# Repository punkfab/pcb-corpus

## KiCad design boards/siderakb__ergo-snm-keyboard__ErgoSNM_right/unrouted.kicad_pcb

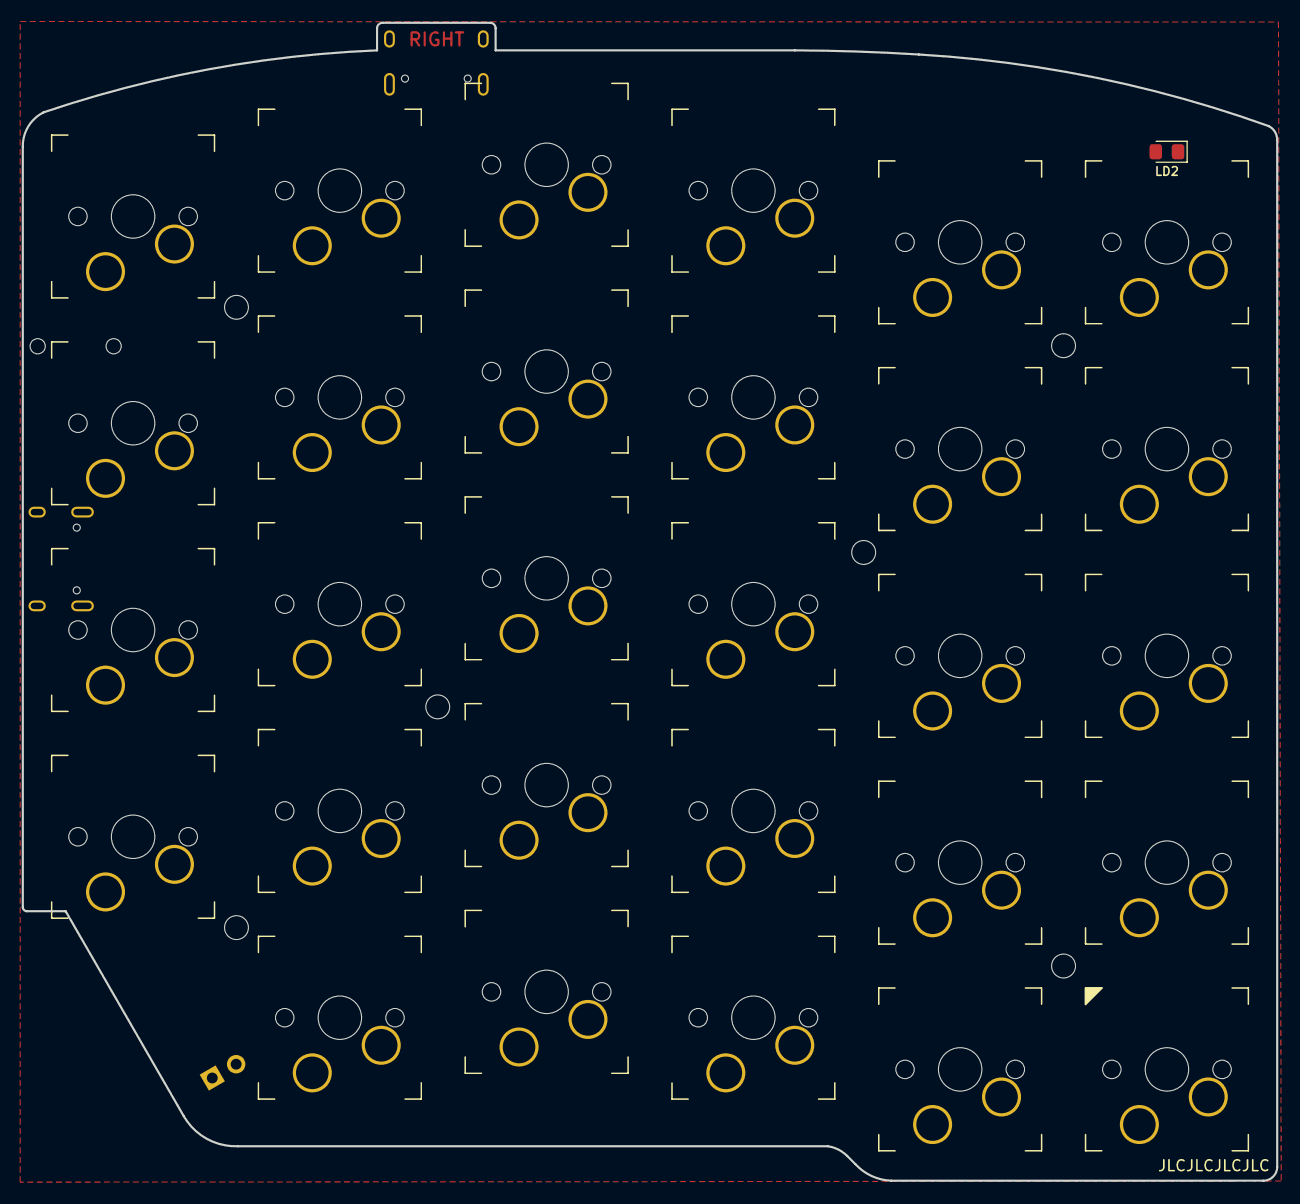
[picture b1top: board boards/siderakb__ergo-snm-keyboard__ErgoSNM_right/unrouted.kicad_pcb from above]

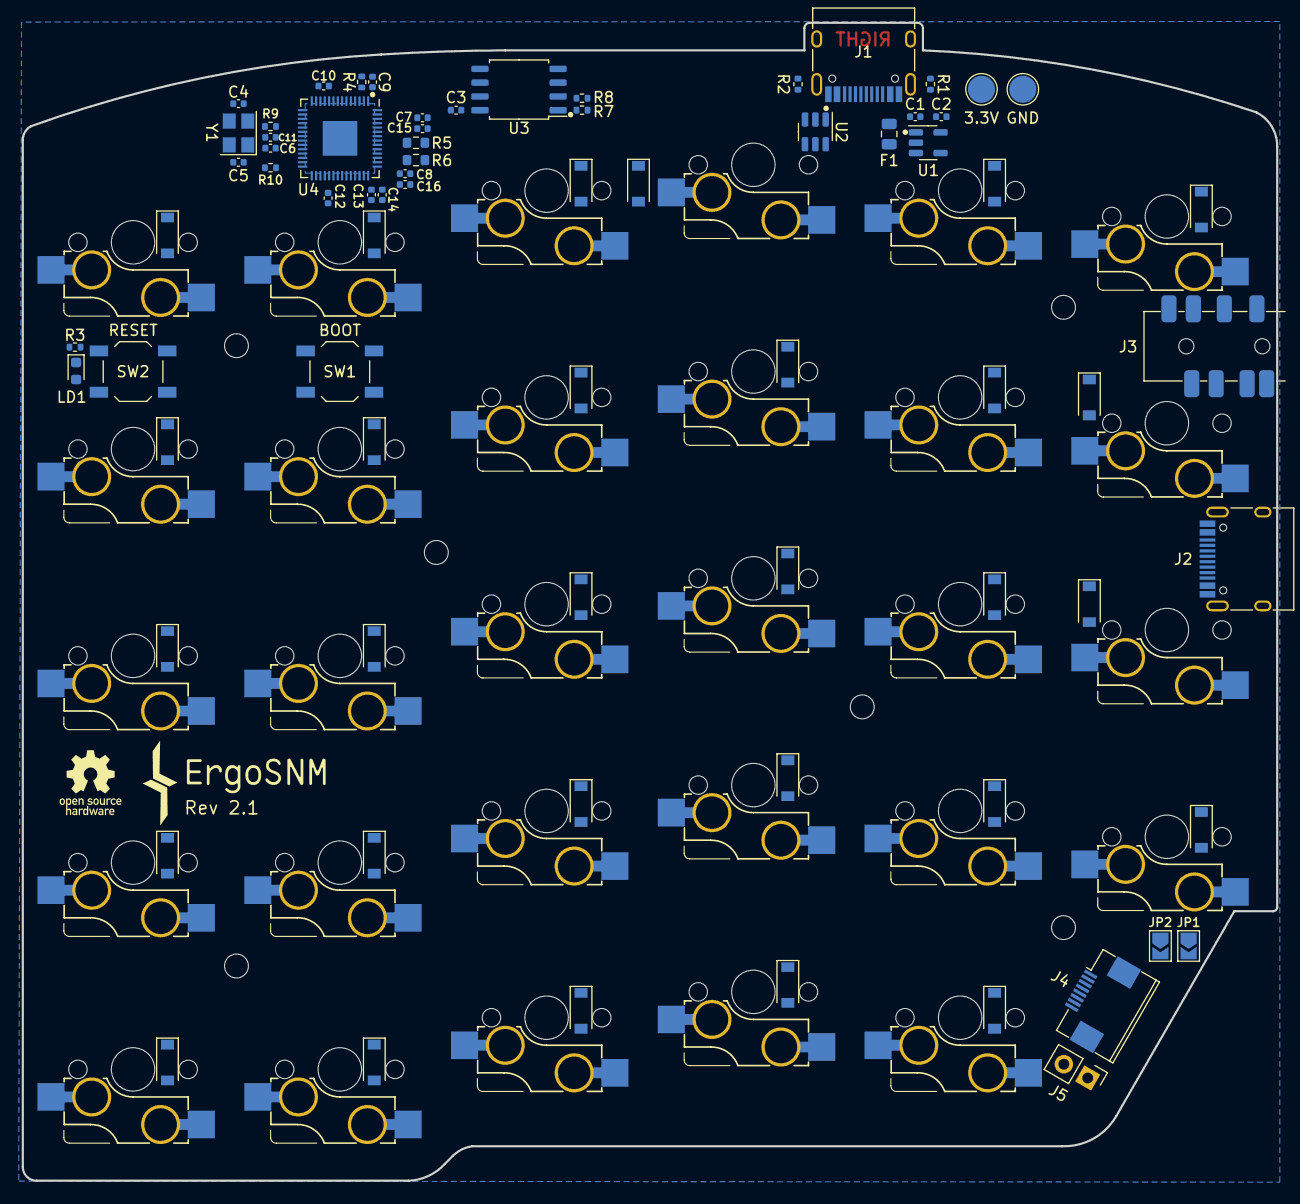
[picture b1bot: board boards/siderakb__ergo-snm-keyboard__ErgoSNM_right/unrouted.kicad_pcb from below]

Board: 2 copper layers, 115.6 x 106.7 mm, 109 parts (73 on the bottom side), 71 nets, no tracks yet.

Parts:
C1, C2, C8, C16: 1uF; C_0402_1005Metric
C3, C6, C7, C9, C10, C11, C12, C13, C14, C15: 100nF; C_0402_1005Metric
C4, C5: 20pF; C_0402_1005Metric
D1, D2, D3, D4, D5, D6, D7, D8, D9, D10, D11, D12, D13, D14, D15, D16, D17, D18, D19, D20, D21, D22, D23, D24, D25, D26, D27, D28, D29: 1N4148; D_SOD-123
F1: 500mA, 6V; Fuse_0805_2012Metric
H1, H2, H3, H4, H5, H6: MountingHole; MountingHole_2.2mm_M2
J1, J2: USB_C_Receptacle_USB2.0; USB_C_Receptacle_HRO_TYPE-C-31-M-12
J3: PJ-393_TRRS_8P; PJ-393 8P TRRS
J4: Conn_01x08; FPC_8P_0.5mm_AFC01-S08FCA-00
J5: Conn_01x02; PinHeader_1x02_P2.54mm_Vertical
JP1, JP2: SolderJumper_2_Open; SolderJumper-2_P1.3mm_Open_TrianglePad1.0x1.5mm
KEY1, KEY2, KEY3, KEY4, KEY5, KEY6, KEY7, KEY8, KEY9, KEY10, KEY11, KEY12, KEY13, KEY14, KEY15, KEY16, KEY17, KEY18, KEY19, KEY20, KEY21, KEY22, KEY23, KEY24, KEY25, KEY26, KEY27, KEY28, KEY29: SW_Push_45deg; MX_switch_PTH_hotswap_A
LD1: Red; LED_0603_1608Metric
LD2: LED; LED_0805_2012Metric_Pad1.15x1.40mm_HandSolder
R1, R2, R4: 5.1k; R_0402_1005Metric
R3, R7, R9: 1k; R_0402_1005Metric
R5, R6: 27; R_0603_1608Metric
R8, R10: 10k; R_0402_1005Metric
SW1: BOOT; SW_SPST_TL3342
SW2: RESET; SW_SPST_TL3342
TP1, TP4: TestPoint; TestPoint_Pad_D2.5mm
U1: RT9013-33GB; SOT-23-5
U2: SRV05-4; SOT-23-6
U3: W25Q128JVS; SOIC-8_5.23x5.23mm_P1.27mm
U4: RP2040; QFN-56-1EP_7x7mm_P0.4mm_EP3.2x3.2mm
Y1: 12MHz; Crystal_SMD_3225-4Pin_3.2x2.5mm

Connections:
+1V1: C6.1, C7.1, C8.1, U4.23 (DVDD), U4.45 (VREG_VOUT), U4.50 (DVDD)
+3V3: C2.1, C3.1, C9.1, C10.1, C11.1, C12.1, C13.1, C14.1, C15.1, C16.1, J2.A4 (VBUS), J2.A9 (VBUS), J2.B4 (VBUS), J2.B9 (VBUS), J3.S, J4.7, R4.2, R8.1, R10.1, TP1.1, U1.5 (VOUT), U3.8 (VCC), U4.1 (IOVDD), U4.10 (IOVDD), U4.22 (IOVDD), U4.33 (IOVDD), U4.42 (IOVDD), U4.43 (ADC_AVDD), U4.44 (VREG_IN), U4.48 (USB_VDD), U4.49 (IOVDD)
+5V: C1.1, F1.2, U1.1 (VIN), U1.3 (EN), U2.5 (VP)
/RP2040/BOOT: R7.1, SW1.2
/RP2040/QSPI_D0: U3.5 (DI(IO0)), U4.53 (QSPI_SD0)
/RP2040/QSPI_D1: U3.2 (DO(IO1)), U4.55 (QSPI_SD1)
/RP2040/QSPI_D2: U3.3 (IO2), U4.54 (QSPI_SD2)
/RP2040/QSPI_D3: U3.7 (IO3), U4.51 (QSPI_SD3)
/RP2040/QSPI_SCLK: U3.6 (CLK), U4.52 (QSPI_SCLK)
/RP2040/QSPI_SS: R7.2, R8.2, U3.1 (~CS), U4.56 (QSPI_SS)
/RP2040/~RESET: R10.2, SW2.2, U4.26 (RUN)
/USB_D+: J1.A6 (D+), J1.B6 (D+), R5.1, U2.3 (IO2)
/USB_D-: J1.A7 (D-), J1.B7 (D-), R6.1, U2.4 (IO3)
COL_0: KEY1.1, KEY7.1, KEY13.1, KEY19.1, KEY25.1, U4.15 (GPIO12)
COL_1: KEY2.1, KEY8.1, KEY14.1, KEY20.1, KEY26.1, U4.29 (GPIO18)
COL_2: KEY3.1, KEY9.1, KEY15.1, KEY21.1, KEY27.1, U4.14 (GPIO11)
COL_3: KEY4.1, KEY10.1, KEY16.1, KEY22.1, KEY28.1, U4.30 (GPIO19)
COL_4: KEY5.1, KEY11.1, KEY17.1, KEY23.1, KEY29.1, U4.37 (GPIO25)
COL_5: J5.1, JP2.1 (A), KEY6.1, KEY12.1, KEY18.1, KEY24.1, U4.39 (GPIO27_ADC1)
GND: C1.2, C2.2, C3.2, C4.1, C5.1, C6.2, C7.2, C8.2, C9.2, C10.2, C11.2, C12.2, C13.2, C14.2, C15.2, C16.2, J1.A1 (GND), J1.A12 (GND), J1.B1 (GND), J1.B12 (GND), J1.S1 (SHIELD), J2.A1 (GND), J2.A12 (GND), J2.B1 (GND), J2.B12 (GND), J2.S1 (SHIELD), J3.T, J4.8, R1.2, R2.2, R3.2, SW1.1, SW2.1, TP4.1, U1.2 (GND), U2.2 (VN), U3.4 (GND), U4.18 (GPIO15), U4.19 (TESTEN), U4.57 (GND), Y1.2, Y1.4
MISO: J4.5, U4.31 (GPIO20)
MOSI: J4.4, U4.35 (GPIO23)
unnamed: C4.2, U4.20 (XIN), Y1.3
unnamed: C5.2, R9.1, Y1.1
unnamed: D1.2 (A), KEY1.2
unnamed: D2.2 (A), KEY2.2
unnamed: D3.2 (A), KEY3.2
unnamed: D4.2 (A), KEY4.2
unnamed: D5.2 (A), KEY5.2
unnamed: D6.2 (A), KEY6.2
unnamed: D7.2 (A), KEY7.2
unnamed: D8.2 (A), KEY8.2
unnamed: D9.2 (A), KEY9.2
unnamed: D10.2 (A), KEY10.2
unnamed: D11.2 (A), KEY11.2
unnamed: D12.2 (A), KEY12.2
unnamed: D13.2 (A), KEY13.2
unnamed: D14.2 (A), KEY14.2
unnamed: D15.2 (A), KEY15.2
unnamed: D16.2 (A), KEY16.2
unnamed: D17.2 (A), KEY17.2
unnamed: D18.2 (A), KEY18.2
unnamed: D19.2 (A), KEY19.2
unnamed: D20.2 (A), KEY20.2
unnamed: D21.2 (A), KEY21.2
unnamed: D22.2 (A), KEY22.2
unnamed: D23.2 (A), KEY23.2
unnamed: D24.2 (A), KEY24.2
unnamed: D25.2 (A), KEY25.2
unnamed: D26.2 (A), KEY26.2
unnamed: D27.2 (A), KEY27.2
unnamed: D28.2 (A), KEY28.2
unnamed: D29.2 (A), KEY29.2
unnamed: J1.A5 (CC1), R1.1
unnamed: J1.B5 (CC2), R2.1
unnamed: J4.1, JP2.2 (B)
unnamed: J4.2, JP1.2 (B)
unnamed: LD1.1 (K), LD2.1 (K), R3.1
unnamed: R5.2, U4.47 (USB_DP)
unnamed: R6.2, U4.46 (USB_DM)
unnamed: R9.2, U4.21 (XOUT)
ROW_0: D1.1 (K), D2.1 (K), D3.1 (K), D4.1 (K), D5.1 (K), D6.1 (K), U4.41 (GPIO29_ADC3)
ROW_1: D7.1 (K), D8.1 (K), D9.1 (K), D10.1 (K), D11.1 (K), D12.1 (K), U4.12 (GPIO9)
ROW_2: D13.1 (K), D14.1 (K), D15.1 (K), D16.1 (K), D17.1 (K), D18.1 (K), U4.8 (GPIO6)
ROW_3: D19.1 (K), D20.1 (K), D21.1 (K), D22.1 (K), D23.1 (K), D24.1 (K), U4.6 (GPIO4)
ROW_4: D25.1 (K), D26.1 (K), D27.1 (K), D28.1 (K), D29.1 (K), J5.2, JP1.1 (A), U4.4 (GPIO2)
SCLK: J4.3, U4.34 (GPIO22)
SERIAL: J2.A6 (D+), J2.B6 (D+), J3.R1, R4.1, U4.2 (GPIO0)
STATE_LED: LD1.2 (A), LD2.2 (A), U4.28 (GPIO17)
VBUS: F1.1, J1.A4 (VBUS), J1.A9 (VBUS), J1.B4 (VBUS), J1.B9 (VBUS)
~CS: J4.6, U4.32 (GPIO21)

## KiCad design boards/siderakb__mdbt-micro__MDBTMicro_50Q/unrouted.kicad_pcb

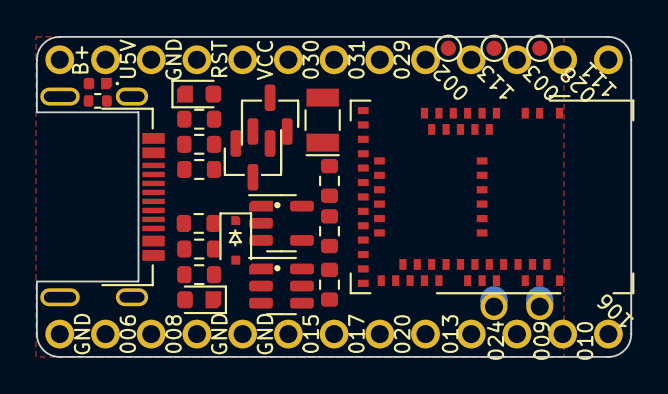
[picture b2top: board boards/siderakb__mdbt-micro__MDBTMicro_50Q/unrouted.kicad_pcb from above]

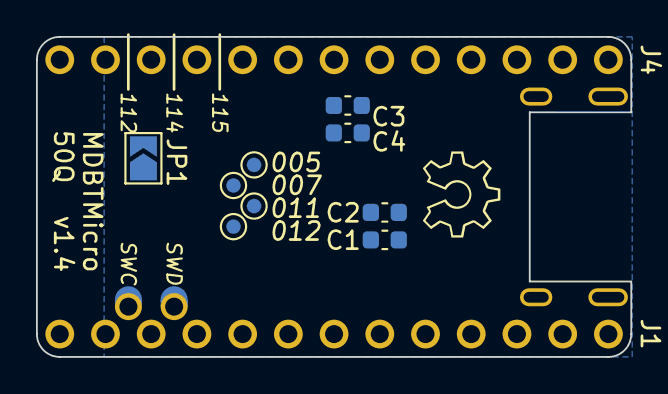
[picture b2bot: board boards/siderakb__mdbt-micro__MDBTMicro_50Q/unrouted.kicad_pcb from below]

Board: 2 copper layers, 33.0 x 17.8 mm, 36 parts (11 on the bottom side), 49 nets, no tracks yet.

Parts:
C1, C2: 1uF; C_0603_1608Metric
C3, C4: 12pF; C_0603_1608Metric
D1: 1N5819; D_SOD-323F
J1, J4: Conn_01x13; PinHeader_1x13_P2.54mm_Vertical
J2: USB_C_Receptacle_USB2.0; USB Type-C Mid-Mount Receptacle 16P
J3: Conn_01x02; PinHeader_1x02_P2.54mm_Vertical
JP1: SolderJumper_2_Open; SolderJumper-2_P1.3mm_Open_TrianglePad1.0x1.5mm
LD1: Red; LED_0603_1608Metric
LD2: Blue; LED_0603_1608Metric
LD3: Green; LED_0402_1005Metric
Q1, Q2: AO3407; SOT-23
R1: 100k; R_0603_1608Metric
R2, R4: 1k; R_0603_1608Metric
R3: Rprog; R_0603_1608Metric
R5: 1k; R_0402_1005Metric
R6: 820k; R_0603_1608Metric
R7, R8: 2M; R_0603_1608Metric
R9, R10: 5.1k; R_0603_1608Metric
TP1, TP2, TP3, TP4, TP5, TP6, TP7: TestPoint; TestPoint_Pad_D1.0mm
U1: XC6220B331MR-G; SOT-23-5
U2: MDBT50Q-x1MV2; Raytac_MDBT50Q
U3: TP4057; SOT-23-6
X1: 32.768kHz; Crystal_SMD_MicroCrystal_CC7V-T1A-2Pin_3.2x1.5mm

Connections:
/P0.02: J4.9, U2.11 (P0.02/AIN0)
/P0.03: J4.11, U2.9 (P0.03/AIN1)
/P0.05: TP4.1, U2.21 (P0.05/AIN3)
/P0.06: J1.2, U2.22 (P0.06)
/P0.07: TP5.1, U2.23 (TRACECLK/P0.07)
/P0.08: J1.3, U2.24 (P0.08)
/P0.09: J1.11, U2.52 (P0.09/NFC1)
/P0.10: J1.12, U2.54 (P0.10/NFC2)
/P0.11: TP6.1, U2.27 (TRACEDATA2/P0.11)
/P0.12: TP7.1, U2.29 (TRACEDATA1/P0.12)
/P0.13: J1.9, U2.37 (P0.13)
/P0.15: J1.6, U2.39 (P0.15)
/P0.17: J1.7, U2.41 (P0.17)
/P0.20: J1.8, U2.44 (P0.20)
/P0.24: J1.10, U2.48 (P0.24)
/P0.28: J4.12, U2.13 (P0.28/AIN4)
/P0.29: J4.8, U2.10 (P0.29/AIN5)
/P0.30: J4.6, U2.14 (P0.30/AIN6)
/P0.31: J4.7, U2.12 (P0.31/AIN7)
/P1.04: JP1.1 (A), U2.56 (P1.04)
/P1.06: J1.13, U2.57 (P1.06)
/P1.11: J4.13, JP1.2 (B), U2.4 (P1.11)
/P1.12: TP1.1, U2.5 (P1.12)
/P1.13: J4.10, U2.6 (P1.13)
/P1.14: TP2.1, U2.7 (P1.14)
/P1.15: TP3.1, U2.8 (P1.15)
BATTERY_PIN: R6.1, R7.2, U2.20 (P0.04/AIN2)
EXT_VCC: J4.5, Q2.3 (D)
GND: C1.2, C2.2, C3.1, C4.1, J1.1, J1.4, J1.5, J2.A1 (GND), J2.A12 (GND), J2.B1 (GND), J2.B12 (GND), J2.S1 (SHIELD), J4.3, R1.2, R3.1, R4.1, R5.1, R7.1, R8.2, R9.2, R10.2, U1.2 (VSS), U2.1 (GND), U2.2 (GND), U2.15 (GND), U2.33 (GND), U2.55 (GND), U3.2 (GND)
LED_PIN: LD2.2 (A), U2.3 (P1.10)
unnamed: C1.1, D1.1 (K), Q1.2 (S), U1.1 (VIN), U1.3 (CE)
unnamed: C3.2, U2.17 (XL1/P0.00), X1.2
unnamed: C4.2, U2.18 (XL2/P0.01), X1.1
unnamed: J2.A5 (CC1), R9.1
unnamed: J2.B5 (CC2), R10.1
unnamed: LD1.1 (K), U3.1 (CHRG)
unnamed: LD1.2 (A), R2.1
unnamed: LD2.1 (K), R4.2
unnamed: LD3.1 (K), R5.2
unnamed: R3.2, U3.6 (PROG)
POWER_PIN: Q2.1 (G), R8.1, U2.26 (TRACEDATA3/P1.09)
RESET: J4.4, U2.40 (~RESET/P0.18)
SWCLK: J3.2, U2.53 (SWDCLK)
SWDIO: J3.1, U2.51 (SWDIO)
USB_D+: J2.A6 (D+), J2.B6 (D+), U2.35 (D+)
USB_D-: J2.A7 (D-), J2.B7 (D-), U2.34 (D-)
VBAT: J4.1, Q1.3 (D), R6.2, U3.3 (BAT)
VBUS: D1.2 (A), J2.A4 (VBUS), J2.A9 (VBUS), J2.B4 (VBUS), J2.B9 (VBUS), J4.2, LD3.2 (A), Q1.1 (G), R1.1, R2.2, U2.32 (VBUS), U3.4 (VCC)
nRF_VDD: C2.1, Q2.2 (S), U1.5 (VOUT), U2.28 (VDD), U2.30 (VDDH)

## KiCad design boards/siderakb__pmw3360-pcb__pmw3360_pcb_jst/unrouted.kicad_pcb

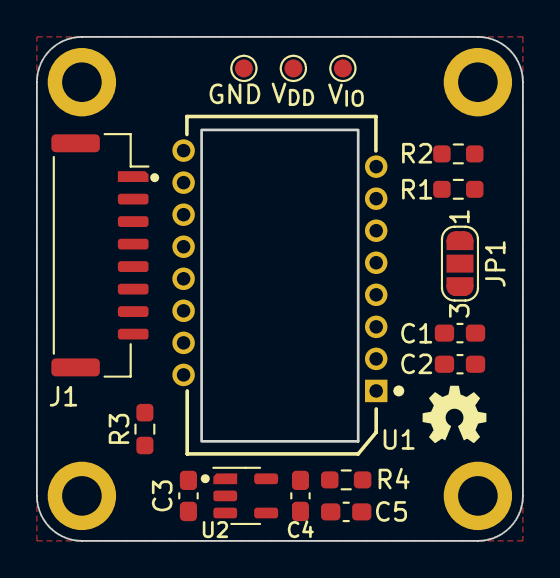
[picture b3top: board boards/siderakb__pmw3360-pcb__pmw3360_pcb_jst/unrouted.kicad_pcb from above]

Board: 2 copper layers, 27.0 x 28.0 mm, 20 parts (0 on the bottom side), 13 nets, no tracks yet.

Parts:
C1: 4.7uF/10V; C_0603_1608Metric_Pad1.08x0.95mm_HandSolder
C2: 100nF; C_0603_1608Metric_Pad1.08x0.95mm_HandSolder
C3: 1uF; C_0603_1608Metric_Pad1.08x0.95mm_HandSolder
C4: 4.7uF; C_0603_1608Metric_Pad1.08x0.95mm_HandSolder
C5: 22nF; C_0603_1608Metric_Pad1.08x0.95mm_HandSolder
H1, H2, H3, H4: MountingHole_Pad; MountingHole_2.2mm_M2_ISO14580_Pad
J1: Conn_01x08; JST_GH_SM08B-GHS-TB_1x08-1MP_P1.25mm_Horizontal
JP1: SolderJumper_3_Open; SolderJumper-3_P1.3mm_Open_RoundedPad1.0x1.5mm_NumberLabels
R1, R2: 10k; R_0603_1608Metric_Pad0.98x0.95mm_HandSolder
R3: 39R; R_0603_1608Metric_Pad0.98x0.95mm_HandSolder
R4: 28k; R_0603_1608Metric_Pad0.98x0.95mm_HandSolder
TP1: V_{IO}; TestPoint_Pad_D1.0mm
TP2: V_{DD}; TestPoint_Pad_D1.0mm
TP3: GND; TestPoint_Pad_D1.0mm
U1: PMW3360DM-T2QU; PMW3360DM-T2QU 16Pin
U2: TLV74318PDBVR; SOT-23-5

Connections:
/CS: J1.6, U1.13 (~CS)
/MISO: J1.5, R2.2, U1.12 (MISO)
/MOSI: J1.4, U1.11 (MOSI)
/MOTION: J1.2, U1.9 (MOTION)
/RESET: J1.1, R1.2, U1.7 (~RESET)
/SCLK: J1.3, U1.10 (SCLK)
GND: C1.2, C2.2, C3.2, C4.2, C5.2, H1.1, H2.1, H3.1, H4.1, J1.8, TP3.1, U1.8 (GND), U2.2 (GND)
unnamed: R3.2, U1.15 (LED_P)
unnamed: C1.1, C2.1, U1.3 (VDDPIX)
unnamed: C5.1, R4.2, U2.4 (NC)
VDD: C4.1, JP1.3 (B), R3.1, R4.1, TP2.1, U1.4 (VDD), U2.5 (OUT)
V_{IN}: C3.1, J1.7, JP1.1 (A), U2.1 (IN), U2.3 (EN)
V_{IO}: JP1.2 (C), R1.1, R2.1, TP1.1, U1.5 (VDDIO)

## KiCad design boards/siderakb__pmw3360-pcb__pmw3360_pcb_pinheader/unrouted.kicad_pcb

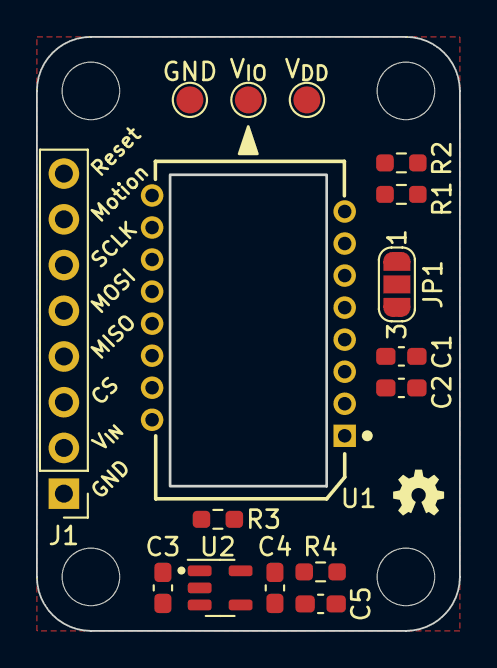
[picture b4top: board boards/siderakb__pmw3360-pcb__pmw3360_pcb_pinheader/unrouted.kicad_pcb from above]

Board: 2 copper layers, 23.5 x 33.0 mm, 20 parts (0 on the bottom side), 13 nets, no tracks yet.

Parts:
C1: 4.7uF/10V; C_0603_1608Metric_Pad1.08x0.95mm_HandSolder
C2: 100nF; C_0603_1608Metric_Pad1.08x0.95mm_HandSolder
C3, C4: 1uF; C_0603_1608Metric_Pad1.08x0.95mm_HandSolder
C5: 22nF; C_0603_1608Metric_Pad1.08x0.95mm_HandSolder
H1, H2, H3, H4: MountingHole_Pad; MountingHole_3.2mm_M3_ISO14580
J1: Conn_01x08; PinHeader_1x08_P2.54mm_Vertical
JP1: SolderJumper_3_Open; SolderJumper-3_P1.3mm_Open_RoundedPad1.0x1.5mm_NumberLabels
R1, R2: 10k; R_0603_1608Metric_Pad0.98x0.95mm_HandSolder
R3: 39R; R_0603_1608Metric_Pad0.98x0.95mm_HandSolder
R4: 28k; R_0603_1608Metric_Pad0.98x0.95mm_HandSolder
TP1: VIO; TestPoint_Pad_D1.5mm
TP2: VDD; TestPoint_Pad_D1.5mm
TP3: GND; TestPoint_Pad_D1.5mm
U1: PMW3360DM-T2QU; PMW3360DM-T2QU 16Pin
U2: TLV74318PDBVR; SOT-23-5

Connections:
/CS: J1.3, U1.13 (~CS)
/MISO: J1.4, R2.2, U1.12 (MISO)
/MOSI: J1.5, U1.11 (MOSI)
/MOTION: J1.7, U1.9 (MOTION)
/RESET: J1.8, R1.2, U1.7 (~RESET)
/SCLK: J1.6, U1.10 (SCLK)
GND: C1.2, C2.2, C3.2, C4.2, C5.2, J1.1, TP3.1, U1.8 (GND), U2.2 (GND)
unnamed: R3.2, U1.15 (LED_P)
unnamed: C1.1, C2.1, U1.3 (VDDPIX)
unnamed: C5.1, R4.2, U2.4 (NC)
VDD: C4.1, JP1.3 (B), R3.1, R4.1, TP2.1, U1.4 (VDD), U2.5 (OUT)
V_{IN}: C3.1, J1.2, JP1.1 (A), U2.1 (IN), U2.3 (EN)
V_{IO}: JP1.2 (C), R1.1, R2.1, TP1.1, U1.5 (VDDIO)

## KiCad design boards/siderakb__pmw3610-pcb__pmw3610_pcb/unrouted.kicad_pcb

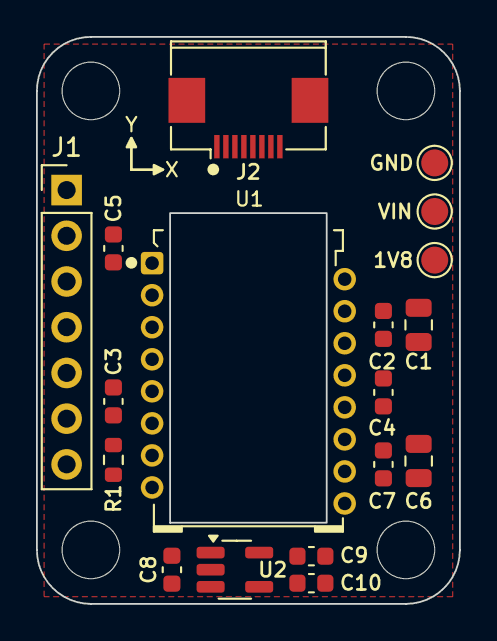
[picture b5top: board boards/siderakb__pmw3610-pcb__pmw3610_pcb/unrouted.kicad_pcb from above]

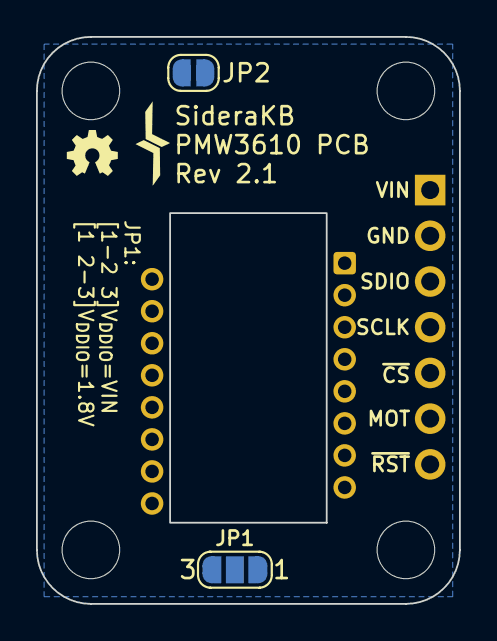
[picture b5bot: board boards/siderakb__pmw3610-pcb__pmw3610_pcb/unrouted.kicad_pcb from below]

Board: 2 copper layers, 23.5 x 31.5 mm, 24 parts (6 on the bottom side), 16 nets, no tracks yet.

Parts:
C1: 3.3uF/16V; C_0805_2012Metric
C2, C3, C4: 100nF; C_0603_1608Metric
C5, C7: 10nF; C_0603_1608Metric
C6: 10uF; C_0805_2012Metric
C8, C9: 1uF; C_0603_1608Metric
C10: 22nF; C_0603_1608Metric
H1, H2, H3, H4: MountingHole; MountingHole_3.2mm_M3_ISO14580
J1: Conn_PinHeader; PinHeader_1x07_P2.54mm_Vertical
J2: Conn_FPC; FPC_8P_0.5mm_AFC01-S08FCA-00
JP1: SolderJumper_3_Open; SolderJumper-3_P1.3mm_Open_RoundedPad1.0x1.5mm_NumberLabels
JP2: FPC_RST; SolderJumper-2_P1.3mm_Open_RoundedPad1.0x1.5mm
R1: 10k; R_0603_1608Metric
TP1, TP2, TP3: TestPoint; TestPoint_Pad_D1.5mm
U1: PMW3610; PMW3610DM-SUDU 16Pin
U2: TLV74318PDBVR; SOT-23-5_HandSoldering

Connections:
+1V8: C1.1, C2.1, C9.1, JP1.3 (B), TP3.1, U1.14 (VDD), U2.5 (OUT)
GND: C1.2, C2.2, C3.2, C5.2, C6.2, C7.2, C8.2, C9.2, C10.2, J1.2, J2.1, TP1.1, U1.11 (GND), U2.2 (GND)
MOTION: J1.6, J2.7, U1.8 (MOTION)
unnamed: J2.8, JP2.2 (B)
unnamed: C5.1, U1.1 (+VCSEL), U1.10 (PASS_T)
unnamed: U1.15 (XYLASER), U1.16 (-VCSEL)
unnamed: C4.2, U1.13 (CN)
unnamed: C4.1, U1.12 (CP)
unnamed: C6.1, C7.1, U1.9 (VCP)
unnamed: C10.1, U2.4 (NC)
SCLK: J1.4, J2.6, U1.3 (SCLK)
SDIO: J1.3, J2.5, U1.2 (SDIO)
VDDIO: C3.1, JP1.2 (C), R1.1, U1.6 (VDDIO)
VIN: C8.1, J1.1, J2.2, JP1.1 (A), TP2.1, U2.1 (IN), U2.3 (EN)
nCS: J1.5, J2.3, U1.5 (NCS)
nRESET: J1.7, JP2.1 (A), R1.2, U1.7 (NRESET)

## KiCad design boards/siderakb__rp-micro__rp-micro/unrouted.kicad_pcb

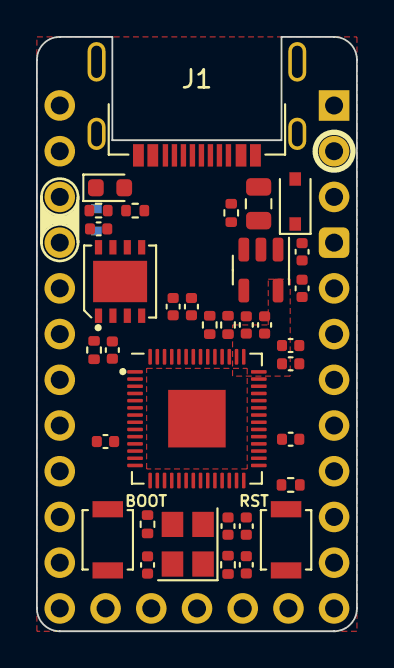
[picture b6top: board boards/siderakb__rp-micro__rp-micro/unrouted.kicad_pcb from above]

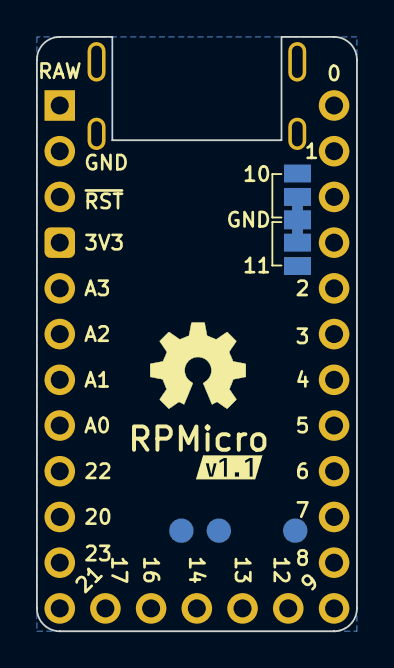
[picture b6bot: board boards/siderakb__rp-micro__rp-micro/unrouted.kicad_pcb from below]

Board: 2 copper layers, 17.8 x 33.0 mm, 44 parts (8 on the bottom side), 54 nets, no tracks yet.

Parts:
C1, C2, C5, C6, C8, C9, C10, C11, C12, C15: 100nF; C_0402_1005Metric
C3, C4: 20pF; C_0402_1005Metric
C7, C13, C14, C16: 1uF; C_0402_1005Metric
D1: B5817; D_SOD-323_HandSoldering
F1: 500mA, 6V; Fuse_0805_2012Metric
J1: USB_C_Receptacle_USB2.0; USB Type-C Mid-Mount Receptacle 16P
J2, J4: Conn_01x12; PinHeader_1x12_P2.54mm_Vertical
J3: Conn_01x05; PinHeader_1x05_P2.54mm_Vertical
LD1: BLUE; LED_0603_1608Metric
R1, R2: 27; R_0402_1005Metric
R3, R4, R9: 1k; R_0402_1005Metric
R5, R8: 10k; R_0402_1005Metric
R6, R7: 5.1k; R_0402_1005Metric
SB1, SB2: SolderJumper_3_Bridged12; SolderJumper-3_P1.3mm_Bridged12_Pad1.0x1.5mm
SW1: BOOT; SW_SPST_B3U-1000P
SW2: RESET; SW_SPST_B3U-1000P
TP1: BOOT; TestPoint_Pad_D2.0mm
TP2: SWDIO; TestPoint_Pad_D2.0mm
TP3: SWCLK; TestPoint_Pad_D2.0mm
U1: RP2040; QFN-56-1EP_7x7mm_P0.4mm_EP3.2x3.2mm
U2: W25Q64JVXGIQ; XSON-8 (4x4mm)
U3: RT9013-33GB; SOT-23-5
Y1: 12MHz; Crystal_SMD_3225-4Pin_3.2x2.5mm
kibuzzard-637CA201: G***; kibuzzard-637CA201

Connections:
0_TX0: J2.1, U1.2 (GPIO0)
1_RX0: J2.2, U1.3 (GPIO1)
2: J2.5, U1.4 (GPIO2)
3: J2.6, U1.5 (GPIO3)
4: J2.7, U1.6 (GPIO4)
5: J2.8, U1.7 (GPIO5)
6: J2.9, U1.8 (GPIO6)
7: J2.10, U1.9 (GPIO7)
8_TX1: J2.11, U1.11 (GPIO8)
9_RX1: J2.12, U1.12 (GPIO9)
10: SB1.3 (B), U1.13 (GPIO10)
11: SB2.3 (B), U1.14 (GPIO11)
12: J3.1, U1.15 (GPIO12)
13: J3.2, U1.16 (GPIO13)
14: J3.3, U1.17 (GPIO14)
16: J3.4, U1.27 (GPIO16)
17: J3.5, U1.28 (GPIO17)
20_MISO: J4.10, U1.31 (GPIO20)
21_CS: J4.12, U1.32 (GPIO21)
22_SCLK: J4.9, U1.34 (GPIO22)
23_MOSI: J4.11, U1.35 (GPIO23)
+1V1: C1.1, C5.1, C7.1, U1.23 (DVDD), U1.45 (VREG_VOUT), U1.50 (DVDD)
+3V3: C2.1, C6.1, C8.1, C9.1, C10.1, C11.1, C12.1, C13.1, C15.1, C16.1, J4.4, R5.1, R8.1, U1.1 (IOVDD), U1.10 (IOVDD), U1.22 (IOVDD), U1.33 (IOVDD), U1.42 (IOVDD), U1.43 (ADC_AVDD), U1.44 (VREG_IN), U1.48 (USB_VDD), U1.49 (IOVDD), U2.8 (VCC), U3.5 (VOUT)
+5V: D1.2 (A), F1.2
/RPD+: R1.2, U1.47 (USB_DP)
/RPD-: R2.2, U1.46 (USB_DM)
A0: J4.8, U1.38 (GPIO26_ADC0)
A1: J4.7, U1.39 (GPIO27_ADC1)
A2: J4.6, U1.40 (GPIO28_ADC2)
A3: J4.5, U1.41 (GPIO29_ADC3)
BOOT: R4.1, SW1.2, TP1.1
GND: C1.2, C2.2, C3.1, C4.1, C5.2, C6.2, C7.2, C8.2, C9.2, C10.2, C11.2, C12.2, C13.2, C14.2, C15.2, C16.2, J1.A1 (GND), J1.A12 (GND), J1.B1 (GND), J1.B12 (GND), J1.S1 (SHIELD), J4.2, R6.2, R7.2, R9.2, SB1.1 (A), SB2.1 (A), SW1.1, SW2.1, U1.19 (TESTEN), U1.57 (GND), U2.4 (GND), U3.2 (GND), Y1.2, Y1.4
unnamed: C3.2, U1.20 (XIN), Y1.3
unnamed: C4.2, R3.1, Y1.1
unnamed: J1.A5 (CC1), R6.1
unnamed: J1.B5 (CC2), R7.1
unnamed: LD1.1 (K), R9.1
unnamed: R3.2, U1.21 (XOUT)
QSPI_CS: R4.2, R5.2, U1.56 (QSPI_SS), U2.1 (~CS)
QSPI_D0: U1.53 (QSPI_SD0), U2.5 (DI(IO0))
QSPI_D1: U1.55 (QSPI_SD1), U2.2 (DO(IO1))
QSPI_D2: U1.54 (QSPI_SD2), U2.3 (IO2)
QSPI_D3: U1.51 (QSPI_SD3), U2.7 (IO3)
QSPI_SCLK: U1.52 (QSPI_SCLK), U2.6 (CLK)
RAW: C14.1, D1.1 (K), J4.1, U3.1 (VIN), U3.3 (EN)
SB1_OUT: J2.3, SB1.2 (C)
SB2_OUT: J2.4, SB2.2 (C)
STATE_LED: LD1.2 (A), U1.37 (GPIO25)
SWCLK: TP3.1, U1.24 (SWCLK)
SWDIO: TP2.1, U1.25 (SWD)
USB_D+: J1.A6 (D+), J1.B6 (D+), R1.1
USB_D-: J1.A7 (D-), J1.B7 (D-), R2.1
VBUS: F1.1, J1.A4 (VBUS), J1.A9 (VBUS), J1.B4 (VBUS), J1.B9 (VBUS)
~RESET: J4.3, R8.2, SW2.2, U1.26 (RUN)

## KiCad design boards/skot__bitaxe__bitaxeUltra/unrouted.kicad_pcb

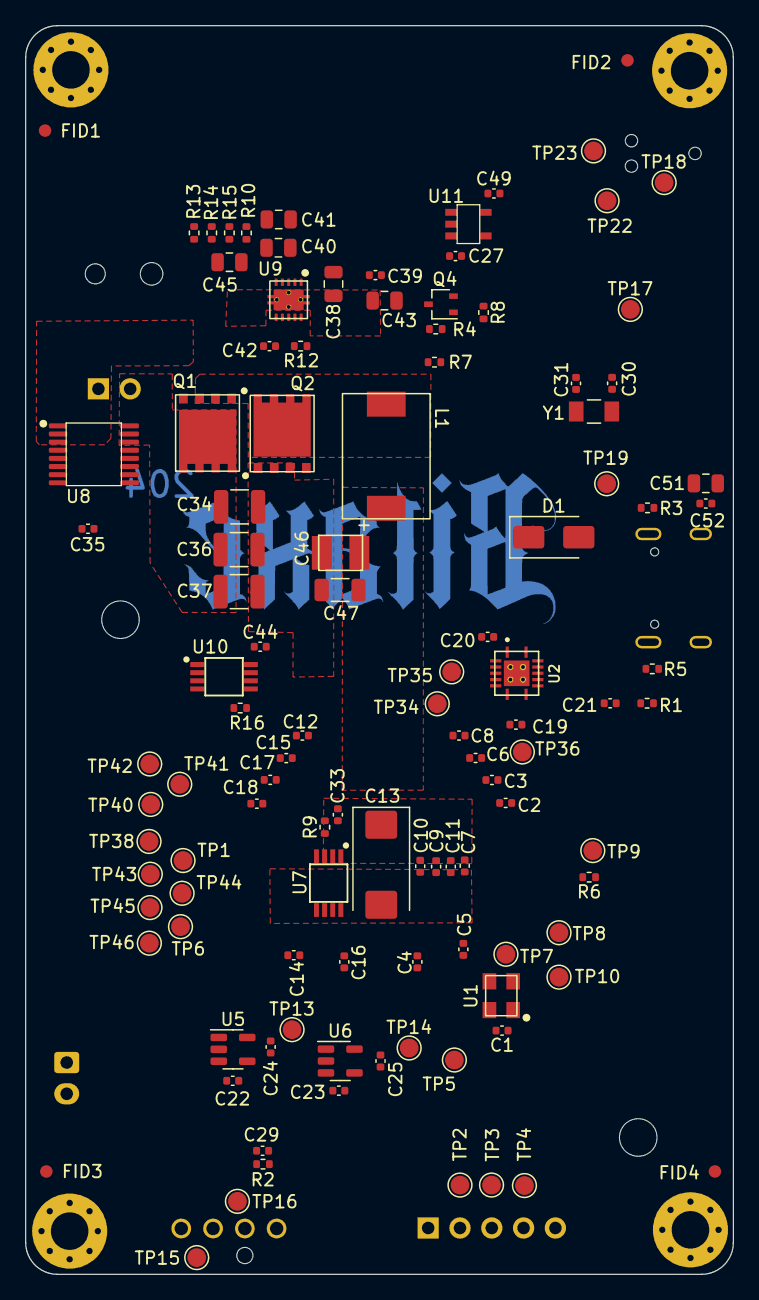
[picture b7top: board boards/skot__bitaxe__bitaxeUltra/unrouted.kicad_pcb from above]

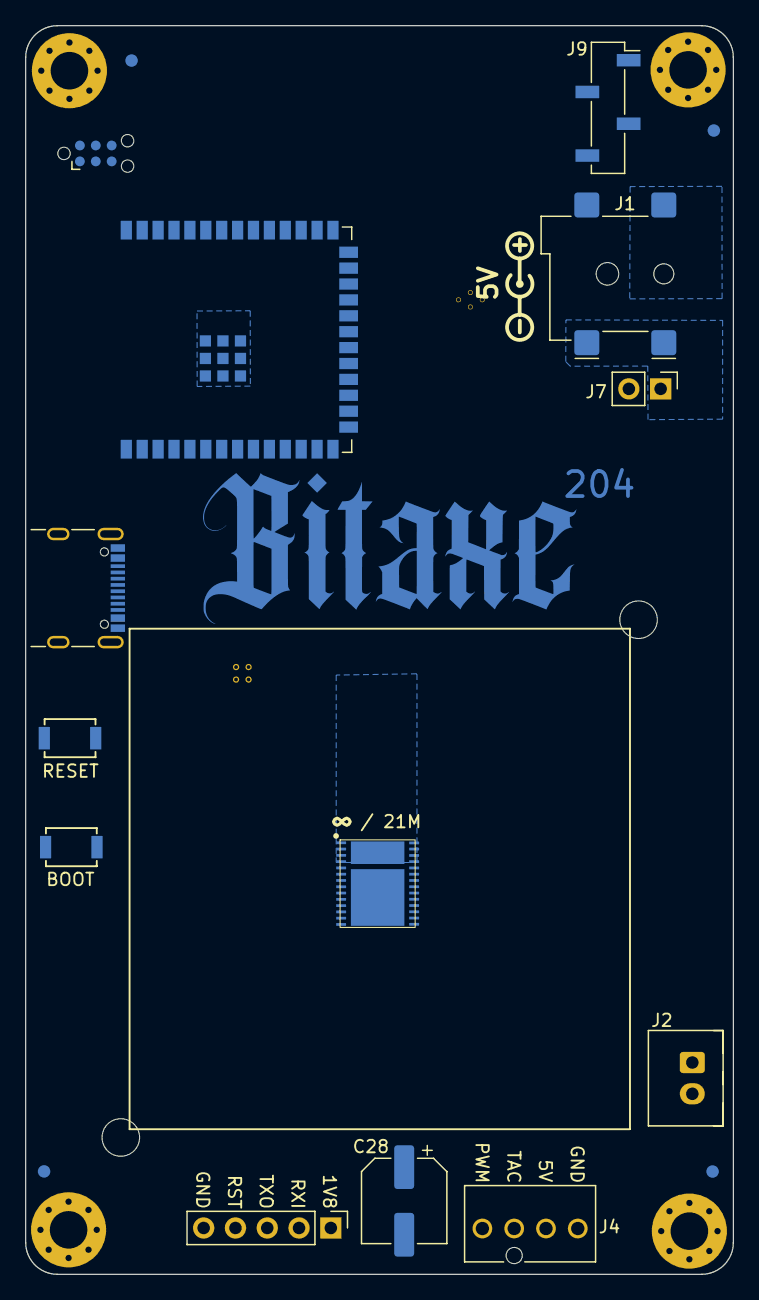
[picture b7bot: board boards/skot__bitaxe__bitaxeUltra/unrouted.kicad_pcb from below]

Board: 4 copper layers, 56.5 x 99.8 mm, 135 parts (18 on the bottom side), 61 nets, no tracks yet.

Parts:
C1, C7, C9, C19, C20, C29, C33, C42, C52: 0.1uF; C_0402_1005Metric
C2, C3, C4, C5, C6, C8, C10, C11, C12, C14, C15, C16, C17, C18, C21, C22, C23, C24, C25, C27, C35, C44, C49: 1uF; C_0402_1005Metric
C13: 330uF; CP_EIA-7343-31_Kemet-D_Pad2.25x2.55mm_HandSolder
C28: 220uF; CP_Elec_6.3x7.7
C30, C31: 6.8pF; C_0402_1005Metric
C34, C36, C37: 47uF; C_1210_3225Metric
C38: 1uF; C_0805_2012Metric
C39: 3.3nF; C_0402_1005Metric
C40: 180pF; C_0805_2012Metric
C41: 1.5nF; C_0805_2012Metric
C43, C51: 10uF; C_0805_2012Metric
C45: 470pF; C_0805_2012Metric
C46: 220uF; CAP_2R5TPE220MAFB
C47: 100uF; C_1206_3216Metric
D1: SS310; D_SMA
FID1, FID2, FID3, FID4, FID5, FID6, FID7, FID8: Fiducial; Fiducial_1mm_Mask2mm
H5, H6: MountingHole; MountingHole_3.5mm
H7, H8, H9, H10: MountingHole_Pad; MountingHole_3mm_Pad_Via
J1: 54-00164; BarrelJack_Wuerth_694106106102_2.0x5.5mm
J2: Conn_01x02; JST_XH_B2B-XH-A_1x02_P2.50mm_Vertical
J3: Conn_01x05; PinHeader_1x05_P2.54mm_Vertical
J4: Conn_01x04; 470531000
J5: TC2030-IDC; Tag-Connect_TC2030-IDC-NL_2x03_P1.27mm_Vertical
J7: Conn_01x02; PinHeader_1x02_P2.54mm_Vertical
J8: USB_C_Receptacle_USB2.0; USB_C_Receptacle_GCT_USB4105-xx-A_16P_TopMnt_Horizontal
J9: Conn_01x04; PinSocket_1x04_P2.54mm_Vertical_SMD_Pin1Right
L1: 150nH; FP1005R1-R15-R
Q1, Q2: CSD17311Q5
Q4: 2N7002K; SOT-323_SC-70
R1, R4, R6, R7, R9: 10k; R_0402_1005Metric
R2: 5.6k; R_0402_1005Metric
R3, R5: 5.1k; R_0402_1005Metric
R8: 1M; R_0402_1005Metric
R10: 3.83k; R_0402_1005Metric
R12: 4.12k; R_0402_1005Metric
R13: 1.33k; R_0402_1005Metric
R14: 4.99k; R_0402_1005Metric
R15: 3.32k; R_0402_1005Metric
R16: 80.6k; R_0402_1005Metric
SW1, SW2: GT-TC029B-H025-L1N; SW_CS1213AGF260_CRS
TP1, TP2, TP3, TP4, TP5, TP6, TP7, TP8, TP9, TP10, TP13, TP14, TP15, TP16, TP17, TP18, TP19, TP22, TP23, TP34, TP35, TP36, TP38, TP40, TP41, TP42, TP43, TP44, TP45, TP46: TestPoint; TestPoint_Pad_D1.5mm
U1: 25MHz; O 25,0-JO32-B-1V3-1-T1-LF
U2: TXB0104RGYR; TXB0104
U3: polarity
U5: MCP1824T-1802E; SOT-23-5
U6: MCP1824T-0802E; SOT-23-5
U7: EMC2101; TSSOP-8_3x3mm_P0.65mm
U8: INA260; TSSOP-16_4.4x5mm_P0.65mm
U9: TPS40305
U10: DS4432U+; TSSOP-8_3x3mm_P0.65mm
U11: RT9080-33GJ5
U12: ESP32-S3-WROOM-1
U14: BM1366_mode1; BM1366
Y1: 32.768kHz; SC32S-7PF20PPM

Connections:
/3V3: C20.1, C33.1, C35.1, C44.1, C49.1, C51.1, C52.1, J5.2, J9.2, R1.1, R2.2, R4.1, R7.1, R8.1, R9.2, TP19.1, U2.14 (VCCB), U7.1 (VDD), U8.10 (VS), U10.8 (VCC), U11.5 (VOUT), U12.2 (3V3), U12.15 (GPIO3/TOUCH3/ADC1_CH2*)
/5V: C22.1, C23.1, C27.1, C28.1, C29.1, C34.1, C36.1, C37.1, C38.1, D1.1, J2.2, J4.2, J7.2, Q1.5 (D), U5.1 (VIN), U5.3 (EN), U6.1 (VIN), U6.3 (EN), U8.14 (IN-), U8.15 (IN-), U8.16 (IN-), U9.1 (VDD), U11.1 (VIN), U11.3 (EN)
/BM1366/0V8: C4.1, C25.1, TP14.1, U6.5 (VOUT), U14.13 (VDDIO_08_0)
/BM1366/1V8: C1.2, C5.1, C19.1, C24.1, J3.1, TP13.1, U1.1 (EN), U1.4 (VIN), U2.1 (VCCA), U2.8 (OE), U5.5 (VOUT), U14.14 (VDDIO_18_0)
/BM1366/ADDR0: TP8.1, U14.10 (ADDR0)
/BM1366/ADDR1: TP10.1, U14.11 (ADDR1)
/BM1366/BI: R6.2, TP9.1, U14.6 (BI)
/BM1366/BO: TP1.1, U14.23 (BO)
/BM1366/CI: J3.2, TP2.1, U2.3 (A2), U14.9 (CI)
/BM1366/CLKI: TP7.1, U1.3 (OUT), U14.8 (CLKI)
/BM1366/CLKO: TP44.1, U14.21 (CLKO)
/BM1366/CO: TP45.1, U14.20 (CO)
/BM1366/INV_CLKO: TP6.1, U14.19 (INV_CLKO)
/BM1366/NRSTO: TP38.1, U14.24 (NRSTO)
/BM1366/PIN_MODE: TP46.1, U14.18 (PIN_MODE)
/BM1366/RI: TP43.1, U14.22 (RI)
/BM1366/RO: J3.3, TP3.1, U2.2 (A1), U14.7 (RO)
/BM1366/RST_N: J3.4, TP4.1, U2.4 (A3), U14.5 (NRSTI)
/BM1366/VDD1_0: C6.2, C8.1, TP34.1, U14.1 (VDD1_0)
/BM1366/VDD1_1: C12.2, C15.1, TP42.1, U14.28 (VDD1_1)
/BM1366/VDD2_0: C3.2, C6.1, TP35.1, U14.2 (VDD2_0)
/BM1366/VDD2_1: C15.2, C17.1, TP41.1, U14.27 (VDD2_1)
/BM1366/VDD3_0: C2.2, C3.1, TP36.1, U14.3 (VDD3_0)
/BM1366/VDD3_1: C17.2, C18.1, TP40.1, U14.26 (VDD3_1)
/ESP32/EN: C21.1, J5.1, R1.2, SW1.2, TP17.1, U12.3 (EN)
/ESP32/IO0: J5.6, SW2.2, TP23.1, U12.27 (GPIO0/BOOT*)
/ESP32/PWR_EN: Q4.1 (G), R7.2, U12.18 (GPIO10/TOUCH10/ADC1_CH9/FSPICS0/FSPIIO4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)
/ESP32/P_RX: J5.5, TP22.1, U12.36 (U0RXD/GPIO44/CLK_OUT2)
/ESP32/P_TX: J5.3, TP18.1, U12.37 (U0TXD/GPIO43/CLK_OUT1)
/ESP32/XIN32: C30.1, U12.8 (GPIO15/U0RTS/ADC2_CH4/XTAL_32K_P), Y1.1
/ESP32/XOUT32: C31.1, U12.9 (GPIO16/U0CTS/ADC2_CH5/XTAL_32K_NH5), Y1.2
/Fan/FAN_PWM: J4.4, R9.1, TP15.1, U7.4 (FAN)
/Fan/FAN_TACH: J4.3, R2.1, TP16.1, U7.6 (ALERT/TACH)
/PLUG_SENSE: J1.3, R8.2, U12.20 (GPIO12/TOUCH12/ADC2_CH1/FSPICLK/FSPIIO6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)
/Power/OUT0: C40.2, C45.2, R10.2, R14.2, R15.1, U9.5 (FB), U10.6 (OUT0)
/Power/PGOOD: R4.2, U9.3 (PGOOD), U12.19 (GPIO11/TOUCH11/ADC2_CH0/FSPID/FSPIIO5/S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)
/Power/SW: C42.2, L1.1, Q1.1, Q1.2, Q1.3 (S), Q2.5 (D), U9.8 (SW)
/Power/VIN: J1.1, J7.1, U8.1 (IN+), U8.2 (IN+), U8.3 (IN+), U8.12 (VBUS)
/RST: U2.11 (B3), U12.39 (GPIO1/TOUCH1/ADC1_CH0)
/RX: U2.13 (B1), U12.11 (GPIO18/U1RXD/ADC2_CH7/CLK_OUT3)
/SCL: J9.3, U7.8 (SMCLK), U8.9 (SCL), U10.2 (SCL), U12.25 (GPIO48/SPICLK_N/SUBSPICLK_N_DIFF)
/SDA: J9.4, U7.7 (SMDATA), U8.8 (SDA), U10.1 (SDA), U12.24 (GPIO47/SPICLK_P/SUBSPICLK_P_DIFF)
/TX: U2.12 (B2), U12.10 (GPIO17/U1TXD/ADC2_CH6)
/VDD: C7.1, C8.2, C9.1, C10.1, C11.1, C12.1, C13.1, C46.1, C47.1, L1.2, R13.1, R14.1, U12.38 (GPIO2/TOUCH2/ADC1_CH1), U14.29 (VDD)
GND: C1.1, C2.1, C4.2, C5.2, C7.2, C9.2, C10.2, C11.2, C13.2, C14.2, C16.2, C18.2, C19.2, C20.2, C21.2, C22.2, C23.2, C24.2, C25.2, C27.2, C28.2, C29.2, C30.2, C31.2, C33.2, C34.2, C35.2, C36.2, C37.2, C38.2, C39.2, C43.2, C44.2, C46.2, C47.2, C49.2, C51.2, C52.2, H7.1, H8.1, H9.1, H10.1, J1.2, J2.1, J3.5, J4.1, J5.4, J8.A1 (GND), J8.A12 (GND), J8.B1 (GND), J8.B12 (GND), J8.S1 (SHIELD), J9.1, Q2.1, Q2.2, Q2.3 (S), Q4.2 (S), R3.1, R5.1, R6.1, R12.2, R15.2, R16.2, SW1.1, SW2.1, TP5.1, U1.2 (GND), U2.5 (A4), U2.7 (GND), U2.10 (B4), U2.15 (GND), U2.16 (GND), U2.17 (GND), U2.18 (GND), U2.19 (GND), U5.2 (GND), U6.2 (GND), U7.5 (GND), U8.4 (A1), U8.5 (A0), U8.6 (GND), U8.11 (GND), U9.11 (GND), U10.4 (GND), U11.2 (GND), U12.1 (GND), U12.40 (GND), U12.41 (GND), U14.4 (VSS), U14.12 (PLL_VSS), U14.17 (VSS), U14.25 (VSS), U14.30 (VSS)
unnamed: C41.2, R10.1
unnamed: C45.1, R13.2
unnamed: D1.2, J8.A4 (VBUS), J8.A9 (VBUS), J8.B4 (VBUS), J8.B9 (VBUS)
unnamed: J8.A5 (CC1), R3.2
unnamed: J8.B5 (CC2), R5.2
unnamed: Q1.4 (G), U9.7 (HDRV)
unnamed: Q2.4 (G), R12.1, U9.9 (LDRV)
unnamed: C39.1, Q4.3 (D), U9.2 (EN/SS)
unnamed: C42.1, U9.6 (BOOT)
unnamed: C43.1, U9.10 (BP)
unnamed: C40.1, C41.1, U9.4 (COMP)
unnamed: R16.1, U10.5 (FS0)
unnamed: J8.A7 (D-), J8.B7 (D-), U12.13 (GPIO19/U1RTS/ADC2_CH8/CLK_OUT2/USB_D-)
unnamed: J8.A6 (D+), J8.B6 (D+), U12.14 (GPIO20/U1CTS/ADC2_CH9/CLK_OUT1/USB_D+)
unnamed: C16.1, U14.16 (VDDIO_08_1)
unnamed: C14.1, U14.15 (VDDIO_18_1)

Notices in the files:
boards/siderakb__ergo-snm-keyboard__ErgoSNM_right/unrouted.kicad_pcb:
Open source hardware, CERN-OHL-P v2
boards/siderakb__mdbt-micro__MDBTMicro_50Q/unrouted.kicad_pcb:
MIT License (Open source hardware)
